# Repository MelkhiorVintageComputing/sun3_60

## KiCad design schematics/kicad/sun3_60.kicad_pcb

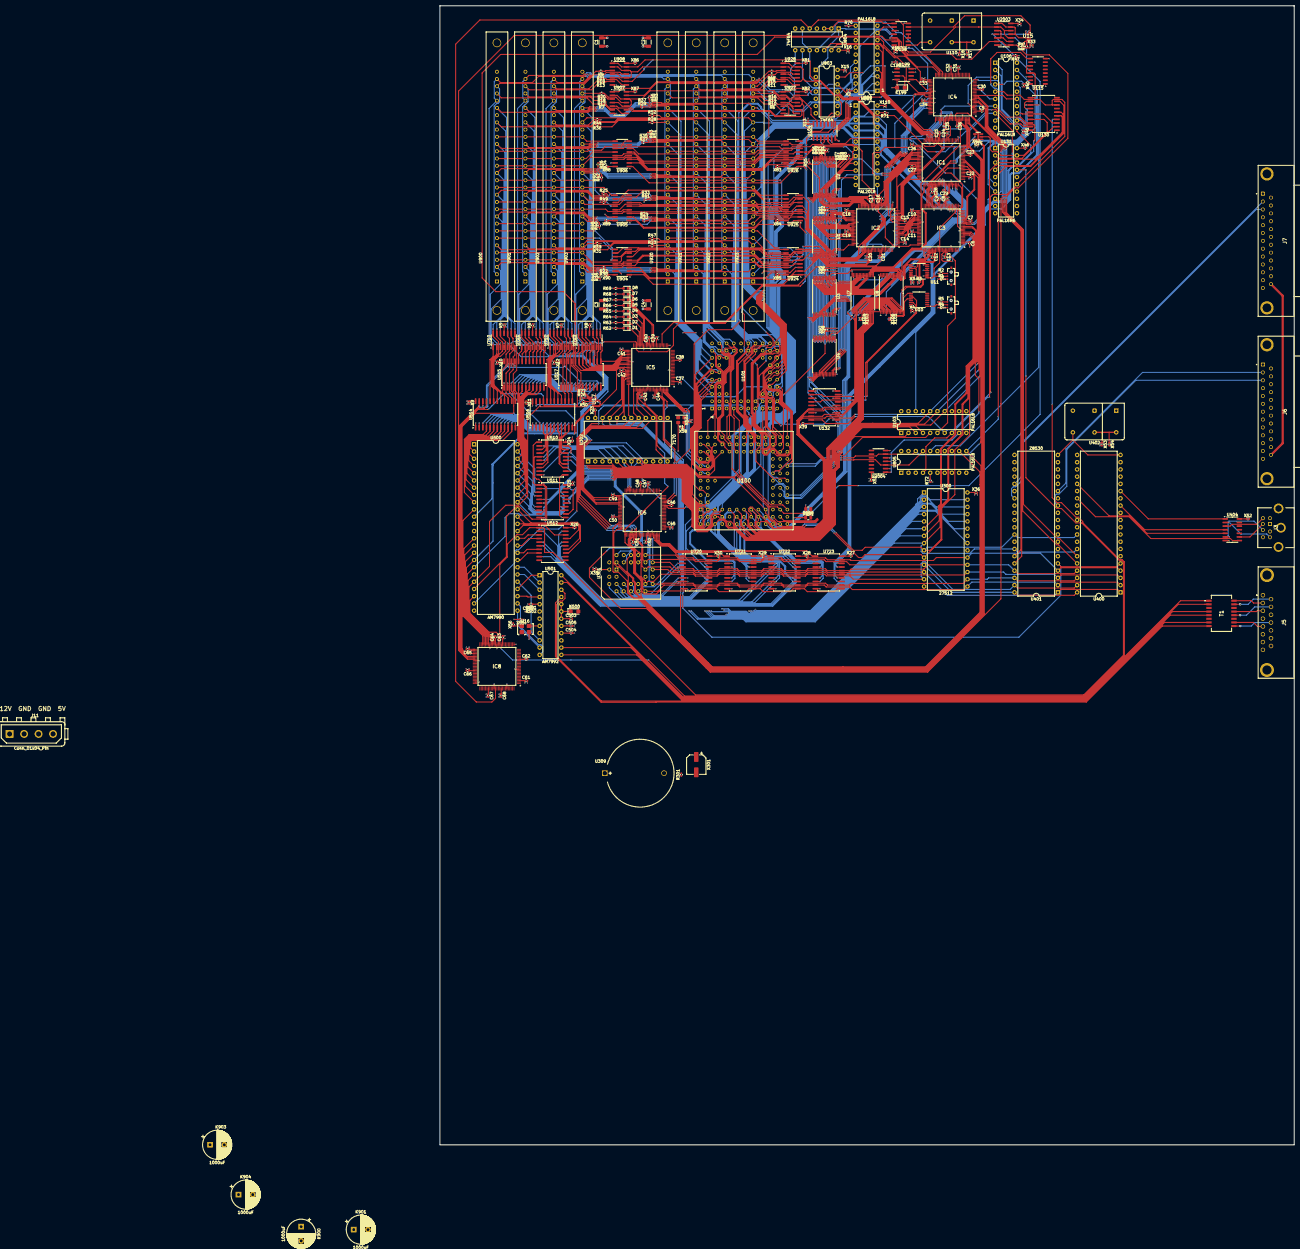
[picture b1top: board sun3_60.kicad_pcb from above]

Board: 4 copper layers, 300.0 x 400.0 mm, 317 parts (0 on the bottom side), 431 nets.

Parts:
C1, C2, C3, C4: 10uF 1206; C_1206_3216Metric
C5, C6, C7, C8, C9, C10, C11, C12, C13, C14, C15, C16, C17, C18, C19, C20, C21, C22, C23, C24, C25, C26, C27, C28, C29, C30, C31, C32, C33, C34, C35, C36, C37, C38, C39, C40, C41, C42, C43, C44, C45, C46, C47, C48, C49, C50, C51, C52, C61, C62, C63, C64, C65, C66, C67, C68, C199, C503, C504: 100nF 0402; C_0402_1005Metric
C502: 680 pF; C_0402_1005Metric
C505: 0.0056uF; C_0402_1005Metric
D1, D2, D3, D4, D5, D6, D7, D8: LED; LED_0603_1608Metric
IC1, IC2, IC3, IC4, IC5, IC6, IC8: ATF1504AS-10AU100; QFP50P1600X1600X120-100N
J3: Mini-DIN-8; 57492681
J5: 5747845-4; 57478454
J6, J7: DB25_Socket; D25S33E4PA00LF
J11: Conn_01x04_Pin; TE_MATE-N-LOK_350211-1_1x04_P5.08mm_Vertical
K199, K500: 10uF tantalum; CP_EIA-3216-18_Kemet-A
K900, K901, K903, K904: 1000uF; CP_Radial_D10.0mm_P5.00mm
R1, R2, R3, R4, R5: 10k; R_0402_1005Metric
R6, R7, R8, R9, R10, R11, R12, R13, R14, R15, R16, R17, R18, R19, R20, R21: 22; R_0402_1005Metric
R22, R23, R24, R25, R26, R27, R28, R29, R30, R31, R32, R33, R34, R35, R36, R37, R38, R39, R40, R41, R42, R43, R44, R45, R46, R47, R48, R49, R50, R51, R52, R53, R55, R56, R57, R58, R59, R60, R61, R70, R71, R72, R75, R76, R77, R78: 4.7k; R_0402_1005Metric
R62, R63, R64, R65, R66, R67, R68, R69: 510; R_0402_1005Metric
R100: 150 ohm 0805; R_0805_2012Metric
R101: 100 ohm 0805; R_0805_2012Metric
R301: 470-OHM; C_0402_1005Metric
R501: 510 Ohm; R_0402_1005Metric
R502: 3K Ohm; R_0402_1005Metric
S1, S2: SSAJ110100; SW_SSAJ110100
T1: TG01-0506NRLTR; TG010506NRLTR
U1, U2, U3, U4, U7, U8: IS61C5128AS-25HLI; TSOP-I-32_11.8x8mm_P0.5mm
U10: CBT3257APW; TSSOP-16_4.4x5mm_P0.65mm
U11: 74CBT3257APW; TSSOP-16_4.4x5mm_P0.65mm
U14: 74LVC1G04; SOT-23-5
U15, U17: 74LVC1G74; 74AVC9112GTX
U16: 20 MHz; Oscillator_SMD_SeikoEpson_SG8002LB-4Pin_5.0x3.2mm
U100: 68020; MC68020RC25
U101: 68881; MC68882_PGA
U103, U106, U800, U805: PAL16L8; DIP-20_W7.62mm
U104: 74F04; SOIC-14_3.9x8.7mm_P1.27mm
U108: 74F00; SOIC-14_3.9x8.7mm_P1.27mm
U110: 40.000 Mhz; CXO_DIP8+14
U115: 74LS590; SO-16_3.9x9.9mm_P1.27mm
U130: 74F374; SOIC-20W_7.5x12.8mm_P1.27mm
U131: PAL16R6; DIP-20_W7.62mm
U132: ALS244; SOIC-20W_7.5x12.8mm_P1.27mm
U199: 7705; SOIC-8_3.9x4.9mm_P1.27mm
U300: 27512; DIP-28_W15.24mm
U301: AT28C64B_PLCC; PLCC-32_THT-Socket
U302: 7170; DIP-24_W15.24mm
U309: 3-VOLT; BatteryHolder_MYOUNG_BS-07-A1BJ001_CR2032
U400, U401: Z8530; DIP-40_W15.24mm
U402: 4.9152 Mhz; CXO_DIP8+14
U404: 74ALS04; SOIC-14_3.9x8.7mm_P1.27mm
U500: AM7990; DIP-48_W15.24mm
U501: AM7992; DIP-24_W7.62mm
U510, U511, U512: ALS373; SOIC-20W_7.5x12.8mm_P1.27mm
U514, U515, U516, U517: ALS652; SOIC-24W_7.5x15.4mm_P1.27mm
U710, U711, U712, U713: ACT11286; SOIC-14_3.9x8.7mm_P1.27mm
U720, U721, U722, U723: ALS374; SOIC-20W_7.5x12.8mm_P1.27mm
U802: PAL20L8; DIP-24_W7.62mm
U803, U804: 74F64; DIP-14_W7.62mm
U900, U901, U902, U903, U920, U921, U922, U923: SIMM
U904, U905, U906, U924, U925, U926: 74AS258; SOIC-16_3.9x9.9mm_P1.27mm
U907, U908, U927, U928: AS1032; SOIC-14_3.9x8.7mm_P1.27mm
U2003: 74AS04; SOIC-14_3.9x8.7mm_P1.27mm
U2004: 74LS125; SOIC-14_3.9x8.7mm_P1.27mm
X2, X3, X4, X5, X6, X7, X8, X9, X10, X11, X12, X13, X14, X15, X16, X17, X23, X24, X25, X26, X27, X28, X29, X30, X33, X34, X35, X36, X39, X40, X41, X42, X46, X47, X50, X51, X52, X53, X55, X57, X81, X82, X83, X84, X85, X86, X87, X88, X89, X90, X91, X93, X95, X97, X103, X105, X110: 100nF 0402; C_0402_1005Metric
X18, X54, X56, X58, X92, X94, X96, X98, X104, X106: 10nF 0402; C_0402_1005Metric
X301: 470UF; CP_Elec_6.3x7.7
Y1: SiT8008xx-2x-xxS; Crystal_SMD_3225-4Pin_3.2x2.5mm

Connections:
+12V: J5.13, J11.1
-5V: J6.25, J7.25
/AS: IC1.40 (I/O_22), IC4.61 (I/O_34), U14.4, U103.9 (I9), U803.12 (A3), U804.9 (D1), U2004.1, U2004.4
/AS-: U14.2, U100.L1 (AS-), U101.H1 (AS-), U130.17 (D3), U131.19 (Q0)
/BERR-: IC8.30 (I/O_15), U100.J2 (BERR-), U106.18 (IO2)
/BERR.T-: IC3.17 (I/O_8), IC4.6 (I/O_1), U106.3 (I3)
/C.S3: IC4.60 (I/O_33), U804.12 (A3)
/C.S3-: IC1.44 (I/O_23), IC4.79 (I/O_44), U803.13 (A4), U805.3 (I3), U904.1 (S), U905.1 (S), U906.1 (S), U924.1 (S), U925.1 (S), U926.1 (S)
/C.S5: IC4.48 (I/O_27), U108.13
/CAS-: IC6.20 (I/O_10), U104.13, U804.8 (Y), U805.2 (I2), U908.2, U908.4, U908.10, U908.12, U928.2, U928.4, U928.10, U928.12
/CLK: IC6.87 (INPUT/GCLK1), U108.12, U803.1 (A1), U804.1 (A1), U2003.6, U2003.8
/CLK-: IC4.90 (INPUT/GCLK2), IC8.87 (INPUT/GCLK1), U115.11 (CPC), U115.13 (CPR), U130.11 (CLK), U131.1 (CLK), U804.5 (C2), U2003.2, U2003.10, U2003.12
/CX0: IC3.76 (I/O_43), U7.20 (A0), U8.17 (A3), U723.13 (D4)
/CX1: IC3.79 (I/O_44), U7.19 (A1), U8.18 (A2), U723.14 (D5)
/CX2: IC3.80 (I/O_45), U7.18 (A2), U8.19 (A1), U723.17 (D6)
/D0: R22.2, U100.K13 (D00), U101.A3 (D00), U514.20 (B1), U710.1 (P2), U900.3 (D0), U920.3 (D0)
/D1: R23.2, U100.K12 (D01), U101.A4 (D01), U514.19 (B2), U710.2 (P1), U900.6 (D1), U920.6 (D1)
/D2: R24.2, U100.L13 (D02), U101.B5 (D02), U514.18 (B3), U710.14 (P3), U900.10 (D2), U920.10 (D2)
/D3: R25.2, U100.L12 (D03), U101.A5 (D03), U514.17 (B4), U710.13 (P4), U900.13 (D3), U920.13 (D3)
/D4: R26.2, U100.M13 (D04), U101.A6 (D04), U514.16 (B5), U710.12 (P5), U900.16 (D4), U920.16 (D4)
/D5: R27.2, U100.M12 (D05), U101.B6 (D05), U514.15 (B6), U710.10 (P6), U900.20 (D5), U920.20 (D5)
/D6: R28.2, U100.M11 (D06), U101.A7 (D06), U514.14 (B7), U710.9 (P7), U900.23 (D6), U920.23 (D6)
/D7: R29.2, U100.L10 (D07), U101.A8 (D07), U514.13 (B8), U710.8, U900.25 (D7), U920.25 (D7)
/D8: R30.2, U100.N12 (D08), U101.A9 (D08), U515.20 (B1), U711.1 (P2), U901.3 (D0), U921.3 (D0)
/D9: R31.2, U100.N11 (D09), U101.C8 (D09), U515.19 (B2), U711.2 (P1), U901.6 (D1), U921.6 (D1)
/D10: R32.2, U100.M10 (D10), U101.B9 (D10), U515.18 (B3), U711.14 (P3), U901.10 (D2), U921.10 (D2)
/D11: R33.2, U100.L9 (D11), U101.B10 (D11), U515.17 (B4), U711.13 (P4), U901.13 (D3), U921.13 (D3)
/D12: R34.2, U100.N10 (D12), U101.D9 (D12), U515.16 (B5), U711.12 (P5), U901.16 (D4), U921.16 (D4)
/D13: R35.2, U100.M9 (D13), U101.C9 (D13), U515.15 (B6), U711.10 (P6), U901.20 (D5), U921.20 (D5)
/D14: R36.2, U100.N9 (D14), U101.C10 (D14), U515.14 (B7), U711.9 (P7), U901.23 (D6), U921.23 (D6)
/D15: R37.2, U100.L8 (D15), U101.D10 (D15), U515.13 (B8), U711.8, U901.25 (D7), U921.25 (D7)
/D16: R38.2, U100.M7 (D16), U101.F10 (D16), U516.20 (B1), U712.1 (P2), U902.3 (D0), U922.3 (D0)
/D17: R39.2, U100.N6 (D17), U101.F9 (D17), U516.19 (B2), U712.2 (P1), U902.6 (D1), U922.6 (D1)
/D18: R40.2, U100.M6 (D18), U101.G10 (D18), U516.18 (B3), U712.14 (P3), U902.10 (D2), U922.10 (D2)
/D19: R41.2, U100.L6 (D19), U101.H10 (D19), U516.17 (B4), U712.13 (P4), U902.13 (D3), U922.13 (D3)
/D20: R42.2, U100.N5 (D20), U101.G9 (D20), U516.16 (B5), U712.12 (P5), U902.16 (D4), U922.16 (D4)
/D21: R43.2, U100.M5 (D21), U101.J10 (D21), U516.15 (B6), U712.10 (P6), U902.20 (D5), U922.20 (D5)
/D22: R44.2, U100.N4 (D22), U101.K10 (D22), U516.14 (B7), U712.9 (P7), U902.23 (D6), U922.23 (D6)
/D23: R45.2, U100.L5 (D23), U101.J9 (D23), U516.13 (B8), U712.8, U902.25 (D7), U922.25 (D7)
/D24: IC3.33 (I/O_18), IC5.63 (I/O_35), R46.2, U100.M4 (D24), U101.K9 (D24), U517.20 (B1), U713.1 (P2), U903.3 (D0), U923.3 (D0)
/D25: IC3.32 (I/O_17), IC5.61 (I/O_34), R47.2, U100.N3 (D25), U101.J7 (D25), U517.19 (B2), U713.2 (P1), U903.6 (D1), U923.6 (D1)
/D26: IC3.31 (I/O_16), IC5.60 (I/O_33), R48.2, U100.M3 (D26), U101.K8 (D26), U517.18 (B3), U713.14 (P3), U903.10 (D2), U923.10 (D2)
/D27: IC3.30 (I/O_15), IC5.58 (I/O_32), R49.2, U100.L4 (D27), U101.K7 (D27), U517.17 (B4), U713.13 (P4), U903.13 (D3), U923.13 (D3)
/D28: IC3.29 (I/O_14), IC5.57 (I/O_31), R50.2, U100.N2 (D28), U101.J6 (D28), U517.16 (B5), U713.12 (P5), U903.16 (D4), U923.16 (D4)
/D29: IC3.21 (I/O_11), IC5.56 (I/O_30), R51.2, U100.M2 (D29), U101.K6 (D29), U517.15 (B6), U713.10 (P6), U903.20 (D5), U923.20 (D5)
/D30: IC3.23 (I/O_12), IC5.54 (I/O_29), R52.2, U100.L3 (D30), U101.K5 (D30), U517.14 (B7), U713.9 (P7), U903.23 (D6), U923.23 (D6)
/D31: IC3.25 (I/O_13), IC5.52 (I/O_28), R53.2, U100.N1 (D31), U101.J5 (D31), U517.13 (B8), U713.8, U903.25 (D7), U923.25 (D7)
/DIS.RAS-: IC1.41 (I/0), U803.11 (A2)
/DISACC-: IC1.45 (I/O_24), IC4.87 (INPUT/GCLK1), U804.13 (A4)
/DMA: U106.12 (IO8), U723.18 (D7)
/DS-: IC4.63 (I/O_35), IC8.67 (I/O_38), U100.M1 (DS-), U101.G1 (DS-)
/DSACK0-: IC1.21 (I/O_11), IC4.94 (I/O_51), IC5.6 (I/O_1), U100.H3 (DSACK0-), U101.J4 (DSACK0-), U106.17 (I03), U805.18 (IO2), U2004.6
/DSACK1-: IC8.16 (I/O_7), U100.J1 (DSACK1-), U101.K4 (DSACK1-), U805.17 (I03), U2004.3
/DXACK-: U130.13 (D7), U805.16 (IO4)
/E.ACK-: IC8.36 (I/O_20), U131.17 (Q2), U510.1 (OE-), U511.1 (OE-), U512.1 (OE-)
/E.CS-: IC8.40 (I/O_22), U17.1 (C), U100.G1 (ECS-), U500.20 (CS-), U516.22 (SBA), U517.22 (SBA)
/E.HOLD-: IC8.44 (I/O_23), U17.2 (D), U500.17 (HOLD-)
/E.IRQ-: IC5.65 (I/O_37), U500.11 (INT-)
/E.REQ-: IC8.35 (I/O_19), U130.4 (D2)
/EN.CAS: IC4.47 (I/O_26), U804.11 (A2)
/EN.DEV-: IC1.23 (I/O_12), IC1.25 (I/O_13), IC4.93 (I/O_50), IC6.30 (I/O_15)
/EN.E-: IC4.45 (I/O_24), IC8.58 (I/O_32)
/EN.UART-: IC1.20 (I/O_10), IC4.8 (I/O_2)
/Ethernet/A0: IC1.48 (I/O_27), IC3.14 (I/O_6), IC6.46 (I/O_25), U100.C4 (A00), U300.10 (A0), U301.11 (A0), U302.8 (A0), U510.2 (Q0), U720.3 (D0), U800.3 (I3)
/Ethernet/A1: IC1.47 (I/O_26), IC3.13 (I/O_5), IC6.47 (I/O_26), U100.A2 (A01), U101.K1 (A01), U300.9 (A1), U301.10 (A1), U302.7 (A1), U400.32 (D/~C), U401.32 (D/~C), U500.21 (ADR), U510.5 (Q1), U720.4 (D1), U800.4 (I4)
/Ethernet/A2: IC3.10 (I/O_4), IC6.48 (I/O_27), U100.E12 (A02), U101.H2 (A02), U300.8 (A2), U301.9 (A2), U302.6 (A2), U400.34 (A/~B), U401.34 (A/~B), U510.6 (Q2), U720.7 (D2), U906.13 (4B), U926.13 (4B)
/Ethernet/A3: IC3.9 (I/O_3), U100.D13 (A03), U101.J1 (A03), U300.7 (A3), U301.8 (A3), U302.5 (A3), U510.9 (Q3), U720.8 (D3), U906.6 (2B), U926.6 (2B)
/Ethernet/A4: IC3.8 (I/O_2), U100.D12 (A04), U101.G2 (A04), U300.6 (A4), U301.7 (A4), U302.4 (A4), U510.12 (Q4), U720.13 (D4), U904.3 (1B), U924.3 (1B)
/Ethernet/A5: U100.C13 (A05), U300.5 (A5), U301.6 (A5), U510.15 (Q5), U720.14 (D5), U904.6 (2B), U924.6 (2B)
/Ethernet/A6: U100.B13 (A06), U300.4 (A6), U301.5 (A6), U510.16 (Q6), U720.17 (D6), U904.10 (3B), U924.10 (3B)
/Ethernet/A7: U100.C12 (A07), U300.3 (A7), U301.4 (A7), U510.19 (Q7), U720.18 (D7), U904.13 (4B), U924.13 (4B)
/Ethernet/A8: U100.A13 (A08), U300.25 (A8), U301.24 (A10), U511.2 (Q0), U721.3 (D0), U905.3 (1B), U925.3 (1B)
/Ethernet/A9: U100.C11 (A09), U300.24 (A9), U301.28 (A9), U511.5 (Q1), U721.4 (D1), U905.6 (2B), U925.6 (2B)
/Ethernet/A10: U100.B12 (A10), U300.21 (A10), U301.29 (A8), U511.6 (Q2), U721.7 (D2), U905.10 (3B), U925.10 (3B)
/Ethernet/A11: U100.A12 (A11), U300.23 (A11), U511.9 (Q3), U721.8 (D3), U905.13 (4B), U925.13 (4B)
/Ethernet/A12: U100.C10 (A12), U300.2 (A12), U511.12 (Q4), U721.13 (D4), U906.3 (1B), U926.3 (1B)
/Ethernet/A13: U1.19 (A1), U2.19 (A1), U3.19 (A1), U4.19 (A1), U100.B11 (A13), U103.1 (I1), U300.26 (A13), U511.15 (Q5), U721.14 (D5)
/Ethernet/A14: U1.20 (A0), U2.20 (A0), U3.20 (A0), U4.20 (A0), U100.A11 (A14), U103.2 (I2), U300.27 (A14), U511.16 (Q6), U721.17 (D6)
/Ethernet/A15: U1.18 (A2), U2.18 (A2), U3.18 (A2), U4.18 (A2), U100.B10 (A15), U103.3 (I3), U300.1 (A15), U511.19 (Q7), U721.18 (D7)
/Ethernet/A16: U1.17 (A3), U2.17 (A3), U3.17 (A3), U4.17 (A3), U100.C9 (A16), U103.4 (I4), U512.12 (Q4), U722.3 (D0)
/Ethernet/A17: U7.14 (A6), U8.3 (A8), U100.C8 (A17), U103.5 (I5), U512.15 (Q5), U722.4 (D1)
/Ethernet/A18: U7.15 (A5), U8.2 (A9), U100.B8 (A18), U512.16 (Q6), U722.7 (D2)
/Ethernet/A19: U7.16 (A4), U8.1 (A11), U100.A8 (A19), U512.19 (Q7), U722.8 (D3)
/Ethernet/A20: U7.12 (A12), U8.6 (A18), U100.B7 (A20), U512.2 (Q0), U722.13 (D4)
/Ethernet/A21: U7.11 (A14), U8.7 (A15), U100.C7 (A21), U512.5 (Q1), U722.14 (D5)
/Ethernet/A22: U7.13 (A7), U8.4 (A13), U100.A7 (A22), U512.6 (Q2), U722.17 (D6)
/Ethernet/A23: U7.10 (A16), U8.9 (A17), U100.A6 (A23), U512.9 (Q3), U722.18 (D7)
/Ethernet/A24: U7.31 (A10), U8.31 (A10), U100.B6 (A24), U132.16 (1Y2), U723.3 (D0)
/Ethernet/A25: U7.9 (A17), U8.10 (A16), U100.C6 (A25), U132.3 (2Y4), U723.4 (D1)
/Ethernet/A26: U7.3 (A8), U8.14 (A6), U100.A5 (A26), U132.5 (2Y3), U723.7 (D2)
/Ethernet/A27: U7.4 (A13), U8.13 (A7), U100.B5 (A27), U132.18 (1Y1), U723.8 (D3)
/Ethernet/A28: IC1.90 (INPUT/GCLK2), U10.14, U100.A4 (A28), U132.14 (1Y3)
/Ethernet/A29: IC1.89 (INPUT/GCLR), U100.C5 (A29), U132.7 (2Y2)
/Ethernet/A30: IC1.88 (INPUT/OE1), U10.11, U100.B4 (A30), U132.12 (1Y4)
/Ethernet/A31: IC1.87 (INPUT/GCLK1), U100.A3 (A31), U132.9 (2Y1)
/Ethernet/CLK_20MHZ_ETH: U16.3 (OUT), U501.8 (X1)
/Ethernet/E.A16: U500.39 (A16), U512.13 (D4)
/Ethernet/E.A17: U500.38 (A17), U512.14 (D5)
/Ethernet/E.A18: U500.37 (A18), U512.17 (D6)
/Ethernet/E.A19: U500.36 (A19), U512.18 (D7)
/Ethernet/E.A20: U500.35 (A20), U512.3 (D0)
/Ethernet/E.A21: U500.34 (A21), U512.4 (D1)
/Ethernet/E.A22: U500.33 (A22), U512.7 (D2)
/Ethernet/E.A23: U500.32 (A23), U512.8 (D3)
/Ethernet/E.ALE: IC8.42 (I/O/PD2), U500.18 (ALE), U510.11 (LE), U511.11 (LE), U512.11 (LE)
/Ethernet/E.BM0-: IC8.46 (I/O_25), U500.15 (LDB-)
/Ethernet/E.BM1-: IC8.45 (I/O_24), U500.16 (VDB-)
/Ethernet/E.CBA: IC8.57 (I/O_31), U514.23 (CBA), U515.23 (CBA), U516.23 (CBA), U517.23 (CBA)
/Ethernet/E.CLSW: U500.28 (COLL), U501.1 (COLL)
/Ethernet/E.CO+: T1.1 (PRI_1), U501.24 (COL+)
/Ethernet/E.CO+<>: J5.2, T1.16 (SEC_6)
/Ethernet/E.CO-: T1.2 (PRI_2), U501.23 (COL-)
/Ethernet/E.CO-<>: J5.9, T1.15 (SEC_5)
/Ethernet/E.D0: U500.9 (DA00), U510.3 (D0), U514.4 (A1), U516.4 (A1)
/Ethernet/E.D1: U500.8 (DA01), U510.4 (D1), U514.5 (A2), U516.5 (A2)
/Ethernet/E.D2: U500.7 (DA02), U510.7 (D2), U514.6 (A3), U516.6 (A3)
/Ethernet/E.D3: U500.6 (DA03), U510.8 (D3), U514.7 (A4), U516.7 (A4)
/Ethernet/E.D4: U500.5 (DA04), U510.13 (D4), U514.8 (A5), U516.8 (A5)
/Ethernet/E.D5: U500.4 (DA05), U510.14 (D5), U514.9 (A6), U516.9 (A6)
/Ethernet/E.D6: U500.3 (DA06), U510.17 (D6), U514.10 (A7), U516.10 (A7)
/Ethernet/E.D7: U500.2 (DA07), U510.18 (D7), U514.11 (A8), U516.11 (A8)
/Ethernet/E.D8: U500.47 (DA08), U511.3 (D0), U515.4 (A1), U517.4 (A1)
/Ethernet/E.D9: U500.46 (DA09), U511.4 (D1), U515.5 (A2), U517.5 (A2)
/Ethernet/E.D10: U500.45 (DA10), U511.7 (D2), U515.6 (A3), U517.6 (A3)
/Ethernet/E.D11: U500.44 (DA11), U511.8 (D3), U515.7 (A4), U517.7 (A4)
/Ethernet/E.D12: U500.43 (DA12), U511.13 (D4), U515.8 (A5), U517.8 (A5)
/Ethernet/E.D13: U500.42 (DA13), U511.14 (D5), U515.9 (A6), U517.9 (A6)
/Ethernet/E.D14: U500.41 (DA14), U511.17 (D6), U515.10 (A7), U517.10 (A7)
/Ethernet/E.D15: U500.40 (DA15), U511.18 (D7), U515.11 (A8), U517.11 (A8)
/Ethernet/E.DAS-: IC8.47 (I/O_26), U500.14 (DAS-)
/Ethernet/E.GAB: IC8.52 (I/O_28), U514.3 (GAB), U515.3 (GAB), U516.3 (GAB), U517.3 (GAB)
/Ethernet/E.GBA0-: IC8.54 (I/O_29), U516.21 (G-BA), U517.21 (G-BA)
/Ethernet/E.GBA1-: IC8.56 (I/O_30), U514.21 (G-BA), U515.21 (G-BA)
/Ethernet/E.HLDA-: IC8.41 (I/0), U500.19 (HLDA-)
/Ethernet/E.RCLK: U500.27 (RCLK), U501.4 (RCLK)
/Ethernet/E.RDY-: IC8.37 (I/O_21), U500.22 (RDY-)
/Ethernet/E.RENA: U500.30 (RXE), U501.3 (RXE)
/Ethernet/E.RX: U500.31 (RX), U501.2 (RX)
/Ethernet/E.RX+: T1.7 (PRI_5), U501.22 (RXD+)
/Ethernet/E.RX+<>: J5.5, T1.10 (SEC_2)
/Ethernet/E.RX-: T1.8 (PRI_6), U501.21 (RXD-)
/Ethernet/E.RX-<>: J5.12, T1.9 (SEC_1)
/Ethernet/E.TCLK: U500.25 (TCLK), U501.11 (TCLK)
/Ethernet/E.TENA: U500.26 (TXE), U501.12 (TXE)
/Ethernet/E.TX: U500.29 (TX), U501.10 (TX)
/Ethernet/E.TX+: T1.4 (PRI_3), U501.14 (TXD+)
/Ethernet/E.TX+<>: J5.3, T1.13 (SEC_4)
/Ethernet/E.TX-: T1.5 (PRI_4), U501.13 (TXD-)
/Ethernet/E.TX-<>: J5.10, T1.12 (SEC_3)
/Ethernet/E.WE-: IC8.48 (I/O_27), U500.10 (R/W-)
/FC0: IC1.10 (I/O_4), U100.E1 (FC0), U103.16 (IO4)
/FC1: IC1.13 (I/O_5), U100.F3 (FC1), U103.15 (IO5)
/FC2: IC1.14 (I/O_6), U100.F2 (FC2), U103.14 (IO6)
/HALT-: IC4.14 (I/O_6), U100.K2 (HALT-), U106.15 (IO5)
/INIT-: IC3.16 (I/O_7), IC4.25 (I/O_13), IC5.84 (I/O_48), IC6.76 (I/O_43), U106.11 (I10), U131.8 (I6), U805.11 (I10)
/IO2CPU-: IC4.92 (I/O_49), IC5.30 (I/O_15)
/IOLOCK-: IC4.52 (I/O_28), U17.5 (Q)
/IPL0-: IC5.100 (I/O_56), U100.J12 (IPL0-)
/IPL1-: IC5.99 (I/O_55), U100.J13 (IPL1-)
/IPL2-: IC5.98 (I/O_54), U100.H12 (IPL2-)
/OE.BOOT-: IC1.33 (I/O_18), IC4.83 (I/O_47)
/P0: U713.3 (P_I/O), U903.26 (O8), U903.29 (I8), U923.26 (O8), U923.29 (I8)
/P1: U712.3 (P_I/O), U902.26 (O8), U902.29 (I8), U922.26 (O8), U922.29 (I8)
/P2: U711.3 (P_I/O), U901.26 (O8), U901.29 (I8), U921.26 (O8), U921.29 (I8)
/P3: U710.3 (P_I/O), U900.26 (O8), U900.29 (I8), U920.26 (O8), U920.29 (I8)
/PD0-: U7.30 (~CE), U8.30 (~CE)
/PD1-: U1.30 (~CE), U2.30 (~CE), U3.30 (~CE), U4.30 (~CE)
/POR-: IC4.58 (I/O_32), U199.5 (RES-)
/R.ACK-: IC1.52 (I/O_28), U103.8 (I8), U106.8 (I8), U108.9, U131.18 (Q1), U800.9 (I9), U802.14 (I14), U805.4 (I4)
/READ-: IC2.36 (I/O_20), IC3.75 (I/O_42), U104.4, U104.5, U906.11 (3A), U926.11 (3A)
/RERUN-: IC4.21 (I/O_11), IC8.93 (I/O_50), U106.6 (I6)
/RESET-: IC5.97 (I/O_53), U100.C1 (RESET-), U101.D1 (RESET-), U106.14 (IO6), U500.23 (RESET-)
/RTC-: IC5.81 (I/O_46), U302.12 (INT-)
/R/W-: IC6.17 (I/O_8), IC8.17 (I/O_8), U100.L2 (R/W-), U101.K2 (R/W-), U104.3
/S8A Memory/CAS: U104.12, U804.6 (C3), U804.10 (D2)
/S8A Memory/CAS0-: U802.22 (IO22), U908.1, U908.5, U908.9, U908.13
/S8A Memory/CAS1-: U802.21 (IO21), U928.1, U928.5, U928.9, U928.13
/S8A Memory/CE-: U802.15 (IO15), U805.1 (I1)
/S8A Memory/M.PDa-: R70.2, U800.11 (I10)
/S8A Memory/M.PDb-: R71.2, U802.23 (I23)
/S8A Memory/M.PDc-: R72.2, U805.5 (I5)
/S8A Memory/PA13: IC2.92 (I/O_49), U1.21 (I/O0), U904.2 (1A), U924.2 (1A)
/S8A Memory/PA14: IC2.85 (I/O/GCLK3), U1.22 (I/O1), U904.5 (2A), U924.5 (2A)
/S8A Memory/PA15: IC2.84 (I/O_48), U1.23 (I/O2), U904.11 (3A), U924.11 (3A)
/S8A Memory/PA16: IC2.83 (I/O_47), U1.25 (I/O3), U904.14 (4A), U924.14 (4A)
/S8A Memory/PA17: IC2.81 (I/O_46), IC4.67 (I/O_38), U1.26 (I/O4), U905.2 (1A), U925.2 (1A)
/S8A Memory/PA18: IC2.80 (I/O_45), IC4.68 (I/O_39), U1.27 (I/O5), U905.14 (4A), U925.14 (4A)
/S8A Memory/PA19: IC2.79 (I/O_44), IC4.69 (I/O_40), U1.28 (I/O6), U905.5 (2A), U925.5 (2A)
/S8A Memory/PA20: IC2.76 (I/O_43), IC4.71 (I/O_41), U1.29 (I/O7), U905.11 (3A), U925.11 (3A)
/S8A Memory/PA21: IC2.48 (I/O_27), U2.21 (I/O0), U906.2 (1A), U926.2 (1A)
/S8A Memory/PA22: IC2.47 (I/O_26), U2.22 (I/O1), U802.7 (I7), U906.5 (2A), U926.5 (2A)
/S8A Memory/PA23: IC2.46 (I/O_25), U2.23 (I/O2), U802.8 (I8), U906.14 (4A), U926.14 (4A)
/S8A Memory/PA24: IC2.45 (I/O_24), U2.25 (I/O3), U802.9 (I9)
/S8A Memory/PA25: IC2.44 (I/O_23), U2.26 (I/O4), U802.10 (I10)
/S8A Memory/PA26: IC2.41 (I/0), U2.27 (I/O5), U802.11 (I11)
/S8A Memory/PA27: IC2.40 (I/O_22), U2.28 (I/O6), U802.13 (I13)
/S8A Memory/PA28: IC2.37 (I/O_21), IC4.64 (I/O_36), U2.29 (I/O7)
/S8A Memory/R.ACK: U108.8, U804.2 (B1), U804.3 (B2)
/S8A Memory/RAS: U104.10, U803.10 (D2)
/S8A Memory/RAS-: U104.11, U803.8 (Y), U907.2, U907.4, U907.10, U907.12, U927.2, U927.4, U927.10, U927.12
/S8A Memory/RE00-: U800.19 (IO1), U907.5, U927.5
/S8A Memory/RE01-: U800.18 (IO2), U907.9, U927.9
/S8A Memory/RE02-: U800.17 (I03), U907.1, U927.1
/S8A Memory/RE03-: U800.16 (IO4), U907.13, U927.13
/SCC.IRQ-: IC5.92 (I/O_49), U400.5 (~INT), U401.5 (~INT)
/SCSI 2, Parity/IO.D0: IC5.80 (I/O_45), IC6.84 (I/O_48), U300.11 (D0), U301.22 (D7), U302.15 (D0), U400.40 (D0), U401.40 (D0), U720.2 (Q0), U721.2 (Q0), U722.2 (Q0), U723.2 (Q0)
/SCSI 2, Parity/IO.D1: IC5.79 (I/O_44), IC6.83 (I/O_47), U300.12 (D1), U301.19 (D4), U302.16 (D1), U400.1 (D1), U401.1 (D1), U720.5 (Q1), U721.5 (Q1), U722.5 (Q1), U723.5 (Q1)
/SCSI 2, Parity/IO.D2: IC5.76 (I/O_43), IC6.81 (I/O_46), U300.13 (D2), U301.15 (D2), U302.17 (D2), U400.39 (D2), U401.39 (D2), U720.6 (Q2), U721.6 (Q2), U722.6 (Q2), U723.6 (Q2)
/SCSI 2, Parity/IO.D3: IC5.75 (I/O_42), IC6.80 (I/O_45), U300.15 (D3), U301.13 (D0), U302.18 (D3), U400.2 (D3), U401.2 (D3), U720.9 (Q3), U721.9 (Q3), U722.9 (Q3), U723.9 (Q3)
/SCSI 2, Parity/IO.D4: IC5.71 (I/O_41), IC6.93 (I/O_50), U300.16 (D4), U301.14 (D1), U302.19 (D4), U400.38 (D4), U401.38 (D4), U720.12 (Q4), U721.12 (Q4), U722.12 (Q4), U723.12 (Q4)
/SCSI 2, Parity/IO.D5: IC5.69 (I/O_40), IC6.94 (I/O_51), U300.17 (D5), U301.18 (D3), U302.20 (D5), U400.3 (D5), U401.3 (D5), U720.15 (Q5), U721.15 (Q5), U722.15 (Q5), U723.15 (Q5)
/SCSI 2, Parity/IO.D6: IC5.68 (I/O_39), IC6.96 (I/O_52), U300.18 (D6), U301.20 (D5), U302.21 (D6), U400.37 (D6), U401.37 (D6), U720.16 (Q6), U721.16 (Q6), U722.16 (Q6), U723.16 (Q6)
/SCSI 2, Parity/IO.D7: IC5.67 (I/O_38), IC6.92 (I/O_49), U300.19 (D7), U301.21 (D6), U302.22 (D7), U400.4 (D7), U401.4 (D7), U720.19 (Q7), U721.19 (Q7), U722.19 (Q7), U723.19 (Q7)
/SCSI 2, Parity/PAR0-: IC6.52 (I/O_28), U713.5 (P_ERR)
/SCSI 2, Parity/PAR1-: IC6.54 (I/O_29), U712.5 (P_ERR)
/SCSI 2, Parity/PAR2-: IC6.56 (I/O_30), U711.5 (P_ERR)
/SCSI 2, Parity/PAR3-: IC6.57 (I/O_31), U710.5 (P_ERR)
/SCSI 2, Parity/PAR.IRQ-: IC5.93 (I/O_50), IC6.21 (I/O_11)
/SCSI 2, Parity/PAR.SAMPLE: IC6.79 (I/O_44), U720.11 (CLK), U721.11 (CLK), U722.11 (CLK), U723.11 (CLK)
/SCSI 2, Parity/PAR.TEST-: IC6.23 (I/O_12), U710.7 (P9)
/SCSI 2, Parity/RD.PAR4-: IC6.100 (I/O_56), U723.1 (OE-)
/SCSI 2, Parity/RD.PAR5-: IC6.99 (I/O_55), U722.1 (OE-)
/SCSI 2, Parity/RD.PAR6-: IC6.98 (I/O_54), U721.1 (OE-)
/SCSI 2, Parity/RD.PAR7-: IC6.97 (I/O_53), U720.1 (OE-)
/SCSI 2, Parity/RD_PARX-: IC4.99 (I/O_55), IC6.75 (I/O_42)
/SCSI 2, Parity/WR_PARX-: IC4.100 (I/O_56), IC6.71 (I/O_41)
/SIMMs 1/CE00-: R9.1, U908.3
/SIMMs 1/CE01-: R13.1, U908.6
/SIMMs 1/CE02-: R19.1, U908.8
/SIMMs 1/CE03-: R21.1, U908.11
/SIMMs 1/M.A0.0: U900.4 (A0), U901.4 (A0), U902.4 (A0), U903.4 (A0), U904.4 (1Y)
/SIMMs 1/M.A1.0: U900.5 (A1), U901.5 (A1), U902.5 (A1), U903.5 (A1), U904.7 (2Y)
/SIMMs 1/M.A2.0: U900.7 (A2), U901.7 (A2), U902.7 (A2), U903.7 (A2), U904.9 (3Y)
/SIMMs 1/M.A3.0: U900.8 (A3), U901.8 (A3), U902.8 (A3), U903.8 (A3), U904.12 (4Y)
/SIMMs 1/M.A4.0: U900.11 (A4), U901.11 (A4), U902.11 (A4), U903.11 (A4), U905.4 (1Y)
/SIMMs 1/M.A5.0: U900.12 (A5), U901.12 (A5), U902.12 (A5), U903.12 (A5), U905.7 (2Y)
/SIMMs 1/M.A6.0: U900.14 (A6), U901.14 (A6), U902.14 (A6), U903.14 (A6), U905.9 (3Y)
/SIMMs 1/M.A7.0: U900.15 (A7), U901.15 (A7), U902.15 (A7), U903.15 (A7), U905.12 (4Y)
/SIMMs 1/M.A8.0: U900.17 (A8), U901.17 (A8), U902.17 (A8), U903.17 (A8), U906.4 (1Y)
/SIMMs 1/M.A9.0: U900.18 (A9), U901.18 (A9), U902.18 (A9), U903.18 (A9), U906.12 (4Y)
/SIMMs 1/M.A10.0: U900.19 (A10), U901.19 (A10), U902.19 (A10), U903.19 (A10), U906.7 (2Y)
/SIMMs 1/M.CE00-: R9.2, U900.2 (CS-), U900.28 (CS8-)
/SIMMs 1/M.CE01-: R13.2, U901.2 (CS-), U901.28 (CS8-)
/SIMMs 1/M.CE02-: R19.2, U902.2 (CS-), U902.28 (CS8-)
/SIMMs 1/M.CE03-: R21.2, U903.2 (CS-), U903.28 (CS8-)
/SIMMs 1/M.RE00-: R7.2, U900.27 (RAS-)
/SIMMs 1/M.RE01-: R12.2, U901.27 (RAS-)
/SIMMs 1/M.RE02-: R18.2, U902.27 (RAS-)
/SIMMs 1/M.RE03-: R20.2, U903.27 (RAS-)
/SIMMs 1/M.WE.0-: U900.21 (WE-), U901.21 (WE-), U902.21 (WE-), U903.21 (WE-), U906.9 (3Y)
/SIMMs 1/XE00-: R7.1, U907.6
/SIMMs 1/XE01-: R12.1, U907.8
/SIMMs 1/XE02-: R18.1, U907.3
/SIMMs 1/XE03-: R20.1, U907.11
/SIMMs 2/CE00-: R8.1, U928.3
/SIMMs 2/CE01-: R11.1, U928.6
/SIMMs 2/CE02-: R15.1, U928.8
/SIMMs 2/CE03-: R17.1, U928.11
/SIMMs 2/M.A0.0: U920.4 (A0), U921.4 (A0), U922.4 (A0), U923.4 (A0), U924.4 (1Y)
/SIMMs 2/M.A1.0: U920.5 (A1), U921.5 (A1), U922.5 (A1), U923.5 (A1), U924.7 (2Y)
/SIMMs 2/M.A2.0: U920.7 (A2), U921.7 (A2), U922.7 (A2), U923.7 (A2), U924.9 (3Y)
/SIMMs 2/M.A3.0: U920.8 (A3), U921.8 (A3), U922.8 (A3), U923.8 (A3), U924.12 (4Y)
/SIMMs 2/M.A4.0: U920.11 (A4), U921.11 (A4), U922.11 (A4), U923.11 (A4), U925.4 (1Y)
/SIMMs 2/M.A5.0: U920.12 (A5), U921.12 (A5), U922.12 (A5), U923.12 (A5), U925.7 (2Y)
/SIMMs 2/M.A6.0: U920.14 (A6), U921.14 (A6), U922.14 (A6), U923.14 (A6), U925.9 (3Y)
/SIMMs 2/M.A7.0: U920.15 (A7), U921.15 (A7), U922.15 (A7), U923.15 (A7), U925.12 (4Y)
/SIMMs 2/M.A8.0: U920.17 (A8), U921.17 (A8), U922.17 (A8), U923.17 (A8), U926.4 (1Y)
/SIMMs 2/M.A9.0: U920.18 (A9), U921.18 (A9), U922.18 (A9), U923.18 (A9), U926.12 (4Y)
/SIMMs 2/M.A10.0: U920.19 (A10), U921.19 (A10), U922.19 (A10), U923.19 (A10), U926.7 (2Y)
/SIMMs 2/M.CE00-: R8.2, U920.2 (CS-), U920.28 (CS8-)
/SIMMs 2/M.CE01-: R11.2, U921.2 (CS-), U921.28 (CS8-)
/SIMMs 2/M.CE02-: R15.2, U922.2 (CS-), U922.28 (CS8-)
/SIMMs 2/M.CE03-: R17.2, U923.2 (CS-), U923.28 (CS8-)
/SIMMs 2/M.RE00-: R6.2, U920.27 (RAS-)
/SIMMs 2/M.RE01-: R10.2, U921.27 (RAS-)
/SIMMs 2/M.RE02-: R14.2, U922.27 (RAS-)
/SIMMs 2/M.RE03-: R16.2, U923.27 (RAS-)
/SIMMs 2/M.WE.0-: U920.21 (WE-), U921.21 (WE-), U922.21 (WE-), U923.21 (WE-), U926.9 (3Y)
/SIMMs 2/XE00-: R6.1, U927.6
/SIMMs 2/XE01-: R10.1, U927.8
/SIMMs 2/XE02-: R14.1, U927.3
/SIMMs 2/XE03-: R16.1, U927.11
/SIZ0: IC8.20 (I/O_10), U100.F1 (SIZ0), U800.1 (I1)
/SIZ1: IC8.19 (I/O_9), U100.G2 (SIZ1), U800.2 (I2)
/V.INT-: IC5.96 (I/O_52), U805.12 (IO8)
/WDOG-: IC3.12 (I/O/PD1), IC4.76 (I/O_43)
/WRITE-: IC1.46 (I/O_25), IC4.88 (INPUT/OE1), IC5.48 (I/O_27), U104.6, U710.6 (XMIT-), U711.6 (XMIT-), U711.7 (P9), U712.6 (XMIT-), U712.7 (P9), U713.6 (XMIT-), U713.7 (P9), U800.7 (I7)
/XACK-: IC6.33 (I/O_18), IC8.29 (I/O_14), U130.15 (Q5), U131.7 (I5)
/sun3_60_cpu/BACK-: U100.A1 (BGACK-), U131.13 (Q6)
/sun3_60_cpu/BERR.P-: IC1.80 (I/O_45), IC3.47 (I/O_26), U106.2 (I2)
/sun3_60_cpu/BERR.V-: IC1.81 (I/O_46), IC3.46 (I/O_25), U106.1 (I1)
/sun3_60_cpu/BERRCLK: IC3.90 (INPUT/GCLK2), U106.19 (IO1)
/sun3_60_cpu/BG-: U100.B2 (BG-), U131.9 (I7)
/sun3_60_cpu/BR-: U100.B3 (BR-), U131.14 (Q5)
/sun3_60_cpu/C.S5-: IC1.42 (I/O/PD2), IC4.80 (I/O_45), U106.7 (I7), U130.18 (D1)
/sun3_60_cpu/C.S7X-: IC1.36 (I/O_20), U130.19 (Q1)
/sun3_60_cpu/CLK1: R100.2, R101.1, U100.C2 (CLK), U101.C2 (CLK), U2003.4
/sun3_60_cpu/CLK2X: U15.1 (C), U108.6
/sun3_60_cpu/CLKA: U15.5 (Q), U2003.1, U2003.11, U2003.13
/sun3_60_cpu/CLKA-: U15.2 (D), U15.3 (~Q), U2003.3, U2003.5, U2003.9
/sun3_60_cpu/CS.FPP-: U101.J3 (CS-), U103.17 (I03)
/sun3_60_cpu/DMA-: U103.7 (I7), U106.5 (I5), U130.8 (D6), U131.15 (Q4), U132.1 (EN1-), U132.19 (EN2-)
/sun3_60_cpu/DMAX-: U130.9 (Q6), U131.5 (I3)
/sun3_60_cpu/E.REX-: U130.5 (Q2), U131.3 (I1)
/sun3_60_cpu/EMULATE-: U103.18 (IO2), U106.4 (I4)
/sun3_60_cpu/EN.BOOT-: IC1.6 (I/O_1), IC3.20 (I/O_10)
/sun3_60_cpu/EN.CTL-: IC1.9 (I/O_3), IC1.83 (I/O_47), IC3.45 (I/O_24)
/sun3_60_cpu/EN.FPP: IC3.92 (I/O_49), U103.6 (I6)
/sun3_60_cpu/PU.2a: R75.2, U15.7 (~PRE)
/sun3_60_cpu/PU.2b: R76.2, U17.7 (~PRE)
/sun3_60_cpu/PU.3a: R78.2, U15.6 (~CLR)
/sun3_60_cpu/PU.3b: R77.2, U17.6 (~CLR)
/sun3_60_cpu/R.CLK-: U106.9 (I9), U115.9 (~RCO)
/sun3_60_cpu/R.REQ-: U106.13 (IO7), U130.3 (D0)
/sun3_60_cpu/R.REX-: U130.2 (Q0), U131.2 (I0)
/sun3_60_cpu/S.REX-: U130.6 (Q4), U131.4 (I2)
/sun3_60_cpu/XACK5-: U130.12 (Q7), U130.14 (D5), U131.6 (I4)
/sun3_60_eeprom/CMCLK_32768_RTC: U302.10 (OIN), Y1.3 (OUT)
/sun3_60_eeprom/LED0: D1.1 (K), IC5.47 (I/O_26)
/sun3_60_eeprom/LED1: D2.1 (K), IC5.46 (I/O_25)
/sun3_60_eeprom/LED2: D3.1 (K), IC5.45 (I/O_24)
/sun3_60_eeprom/LED3: D4.1 (K), IC5.44 (I/O_23)
/sun3_60_eeprom/LED4: D5.1 (K), IC5.41 (I/0)
/sun3_60_eeprom/LED5: D6.1 (K), IC5.40 (I/O_22)
/sun3_60_eeprom/LED6: D7.1 (K), IC5.37 (I/O_21)
/sun3_60_eeprom/LED7: D8.1 (K), IC5.36 (I/O_20)
/sun3_60_eeprom/OE.EPROM-: IC4.44 (I/O_23), U300.22 (~OE)
/sun3_60_eeprom/RD.EEPROM-: IC4.97 (I/O_53), U301.25 (~OE)
/sun3_60_eeprom/RD.INT-: IC4.16 (I/O_7), IC5.20 (I/O_10)
/sun3_60_eeprom/RD.RTC-: IC4.19 (I/O_9), U302.24 (RD-)
/sun3_60_eeprom/RD.SCC0-: IC4.12 (I/O/PD1), U400.36 (~RD)
/sun3_60_eeprom/RD.SCC1-: IC4.10 (I/O_4), U401.36 (~RD)
/sun3_60_eeprom/WR.EEPROM-: IC4.98 (I/O_54), U301.31 (~WE)
/sun3_60_eeprom/WR.INT-: IC4.17 (I/O_8), IC5.19 (I/O_9)
/sun3_60_eeprom/WR.RTC-: IC4.20 (I/O_10), U302.1 (WR-)
/sun3_60_eeprom/WR.SCC0-: IC4.13 (I/O_5), U400.35 (~WR)
/sun3_60_eeprom/WR.SCC1-: IC4.9 (I/O_3), U401.35 (~WR)
/sun3_60_mmu_diag/ACCESS: IC1.64 (I/O_36), IC2.29 (I/O_14), U3.22 (I/O1)
/sun3_60_mmu_diag/CX3: IC3.81 (I/O_46), R3.2, U11.11
/sun3_60_mmu_diag/CX4: IC3.84 (I/O_48), U7.2 (A9), U8.15 (A5)
/sun3_60_mmu_diag/CX5: IC3.83 (I/O_47), U7.1 (A11), U8.16 (A4)
/sun3_60_mmu_diag/EN.PMAP0-: IC1.60 (I/O_33), IC2.32 (I/O_17)
/sun3_60_mmu_diag/EN.PMAP2-: IC1.58 (I/O_32), IC2.33 (I/O_18)
/sun3_60_mmu_diag/EN.PMAP3-: IC1.57 (I/O_31), IC2.35 (I/O_19)
/sun3_60_mmu_diag/EN.SMAP1-: IC1.61 (I/O_34), IC2.31 (I/O_16)
/sun3_60_mmu_diag/EN.SMAP-: IC1.63 (I/O_35), IC2.30 (I/O_15)
/sun3_60_mmu_diag/ENABLE_S3E_V: S2.C, U10.1 (S)
/sun3_60_mmu_diag/MMU0: IC2.6 (I/O_1), IC3.63 (I/O_35)
/sun3_60_mmu_diag/MMU1: IC2.8 (I/O_2), IC3.61 (I/O_34)
/sun3_60_mmu_diag/MMU2: IC2.9 (I/O_3), IC3.60 (I/O_33)
/sun3_60_mmu_diag/MMU3: IC2.10 (I/O_4), IC3.58 (I/O_32)
/sun3_60_mmu_diag/MMU4: IC2.12 (I/O/PD1), IC3.57 (I/O_31)
/sun3_60_mmu_diag/MMU5: IC2.13 (I/O_5), IC3.56 (I/O_30)
/sun3_60_mmu_diag/MMU6: IC2.14 (I/O_6), IC3.54 (I/O_29)
/sun3_60_mmu_diag/MMU7: IC2.16 (I/O_7), IC3.52 (I/O_28)
/sun3_60_mmu_diag/MMU.S: IC1.65 (I/O_37), IC2.17 (I/O_8), U4.23 (I/O2)
/sun3_60_mmu_diag/MMU.V: IC1.71 (I/O_41), IC2.20 (I/O_10), U4.21 (I/O0)
/sun3_60_mmu_diag/MMU.W: IC1.75 (I/O_42), IC2.19 (I/O_9), U4.22 (I/O1)
/sun3_60_mmu_diag/MMU.X: IC2.93 (I/O_50), U4.25 (I/O3)
/sun3_60_mmu_diag/MODIFY: IC1.67 (I/O_38), IC2.25 (I/O_13), U3.25 (I/O3)
/sun3_60_mmu_diag/RD.BERR-: IC1.79 (I/O_44), IC3.48 (I/O_27)
/sun3_60_mmu_diag/RD.CX-: IC1.85 (I/O/GCLK3), IC3.40 (I/O_22)
/sun3_60_mmu_diag/RD.ID-: IC1.8 (I/O_2), IC3.19 (I/O_9)
/sun3_60_mmu_diag/RD.SYSEN-: IC1.94 (I/O_51), IC3.35 (I/O_19)
/sun3_60_mmu_diag/S3E_A28: U7.7 (A15), U8.11 (A14), U10.12
/sun3_60_mmu_diag/S3E_A30: U7.6 (A18), U8.12 (A12), U10.9
/sun3_60_mmu_diag/S3E_CX3: U7.17 (A3), U8.20 (A0), U11.9
/sun3_60_mmu_diag/SA17: IC2.71 (I/O_41), U1.16 (A4), U2.16 (A4), U3.16 (A4), U4.16 (A4), U8.21 (I/O0)
/sun3_60_mmu_diag/SA18: IC2.69 (I/O_40), U1.15 (A5), U2.15 (A5), U3.15 (A5), U4.15 (A5), U8.22 (I/O1)
/sun3_60_mmu_diag/SA19: IC2.68 (I/O_39), U1.14 (A6), U2.14 (A6), U3.14 (A6), U4.14 (A6), U8.23 (I/O2)
/sun3_60_mmu_diag/SA20: IC2.67 (I/O_38), U1.13 (A7), U2.13 (A7), U3.13 (A7), U4.13 (A7), U8.25 (I/O3)
/sun3_60_mmu_diag/SA21: IC2.56 (I/O_30), U1.3 (A8), U2.3 (A8), U3.3 (A8), U4.3 (A8), U7.26 (I/O4)
/sun3_60_mmu_diag/SA22: IC2.57 (I/O_31), U1.2 (A9), U2.2 (A9), U3.2 (A9), U4.2 (A9), U7.27 (I/O5)
/sun3_60_mmu_diag/SA23: IC2.75 (I/O_42), U1.31 (A10), U2.31 (A10), U3.31 (A10), U4.31 (A10), U7.29 (I/O7)
/sun3_60_mmu_diag/SA24: IC2.58 (I/O_32), U1.1 (A11), U2.1 (A11), U3.1 (A11), U4.1 (A11), U7.28 (I/O6)
/sun3_60_mmu_diag/SA25: IC2.65 (I/O_37), R55.1, U1.12 (A12), U2.12 (A12), U3.12 (A12), U4.12 (A12), U8.26 (I/O4)
/sun3_60_mmu_diag/SA26: IC2.64 (I/O_36), R56.1, U1.11 (A14), U2.11 (A14), U3.11 (A14), U4.11 (A14), U8.27 (I/O5)
/sun3_60_mmu_diag/SA27: IC2.54 (I/O_29), R57.1, U1.4 (A13), U2.4 (A13), U3.4 (A13), U4.4 (A13), U7.25 (I/O3)
/sun3_60_mmu_diag/SA28: IC2.60 (I/O_33), R58.1, U1.7 (A15), U2.7 (A15), U3.7 (A15), U4.7 (A15), U7.22 (I/O1)
/sun3_60_mmu_diag/SA29: IC2.63 (I/O_35), R59.1, U1.10 (A16), U2.10 (A16), U3.10 (A16), U4.10 (A16), U8.28 (I/O6)
/sun3_60_mmu_diag/SA30: IC2.61 (I/O_34), R60.1, U1.9 (A17), U2.9 (A17), U3.9 (A17), U4.9 (A17), U7.21 (I/O0)
/sun3_60_mmu_diag/SA31: IC2.52 (I/O_28), R61.1, U1.6 (A18), U2.6 (A18), U3.6 (A18), U4.6 (A18), U7.23 (I/O2)
/sun3_60_mmu_diag/TYPE0: IC1.69 (I/O_40), IC2.21 (I/O_11), IC4.85 (I/O/GCLK3), U3.21 (I/O0)
/sun3_60_mmu_diag/TYPE1: IC1.68 (I/O_39), IC2.23 (I/O_12), IC4.84 (I/O_48), U3.23 (I/O2)
/sun3_60_mmu_diag/WE.PMAP0-: IC1.96 (I/O_52), IC1.97 (I/O_53), U4.5 (~WE)
/sun3_60_mmu_diag/WE.PMAP2-: IC1.54 (I/O_29), U2.5 (~WE)
/sun3_60_mmu_diag/WE.PMAP3-: IC1.56 (I/O_30), U1.5 (~WE)
/sun3_60_mmu_diag/WE.SMAP1-: IC1.99 (I/O_55), U8.5 (~WE)
/sun3_60_mmu_diag/WE.SMAP-: IC1.98 (I/O_54), U7.5 (~WE)
/sun3_60_mmu_diag/WE.STAT-: IC1.76 (I/O_43), U3.5 (~WE)
/sun3_60_mmu_diag/WR.CX-: IC1.84 (I/O_48), IC3.44 (I/O_23)
/sun3_60_mmu_diag/WR.SYSEN-: IC1.93 (I/O_50), IC3.36 (I/O_20)
/sun3_60_serial/RXDC: J6.3, U401.13 (RXDA)
/sun3_60_serial/RXDD: J7.3, U401.27 (RXDB)
/sun3_60_serial/RxDA: J3.6, U404.3
/sun3_60_serial/RxDB: J3.4, U404.9
/sun3_60_serial/SERIAL_PCLK: U400.20 (PCLK), U401.20 (PCLK), U402.8 (OUT)
/sun3_60_serial/TXDC: J6.2, U401.15 (TXDA)
/sun3_60_serial/TXDD: J7.2, U401.25 (TXDB)
/sun3_60_serial/TxDA: J3.5, U404.2
/sun3_60_serial/TxDB: J3.7, U404.6
ENABLE_S3E: IC1.100 (I/O_56), IC3.87 (INPUT/GCLK1), S1.C, U11.1 (S)
GND: C1.2, C2.2, C3.2, C4.2, C5.2, C6.2, C7.2, C8.2, C9.2, C10.2, C11.2, C12.2, C13.2, C14.2, C15.2, C16.2, C17.2, C18.2, C19.2, C20.2, C21.2, C22.2, C23.2, C24.2, C25.2, C26.2, C27.2, C28.2, C29.2, C30.2, C31.2, C32.2, C33.2, C34.2, C35.2, C36.2, C37.2, C38.2, C39.2, C40.2, C41.2, C42.2, C43.2, C44.2, C45.2, C46.2, C47.2, C48.2, C49.2, C50.2, C51.2, C52.2, C61.2, C62.2, C63.2, C64.2, C65.2, C66.2, C67.2, C68.2, C199.2, C502.1, C503.2, C504.2, C505.2, IC1.11 (GND_1), IC1.26 (GND_2), IC1.38 (GND_3), IC1.43 (GND_4), IC1.59 (GND_5), IC1.74 (GND_6), IC1.86 (GND_7), IC1.95 (GND_8), IC2.11 (GND_1), IC2.26 (GND_2), IC2.38 (GND_3), IC2.43 (GND_4), IC2.59 (GND_5), IC2.74 (GND_6), IC2.86 (GND_7), IC2.95 (GND_8), IC3.11 (GND_1), IC3.26 (GND_2), IC3.38 (GND_3), IC3.43 (GND_4), IC3.59 (GND_5), IC3.74 (GND_6), IC3.86 (GND_7), IC3.95 (GND_8), IC4.11 (GND_1), IC4.26 (GND_2), IC4.38 (GND_3), IC4.43 (GND_4), IC4.59 (GND_5), IC4.74 (GND_6), IC4.86 (GND_7), IC4.95 (GND_8), IC5.11 (GND_1), IC5.26 (GND_2), IC5.38 (GND_3), IC5.43 (GND_4), IC5.59 (GND_5), IC5.74 (GND_6), IC5.86 (GND_7), IC5.95 (GND_8), IC6.11 (GND_1), IC6.26 (GND_2), IC6.38 (GND_3), IC6.43 (GND_4), IC6.59 (GND_5), IC6.74 (GND_6), IC6.86 (GND_7), IC6.95 (GND_8), IC8.11 (GND_1), IC8.26 (GND_2), IC8.38 (GND_3), IC8.43 (GND_4), IC8.59 (GND_5), IC8.74 (GND_6), IC8.86 (GND_7), IC8.95 (GND_8), J3.1, J3.2, J5.1, J5.MH1, J5.MH2, J6.7, J7.7, J11.2, J11.3, K199.2, K500.2, K900.2, K901.2, K903.2, K904.2, R2.1, R3.1, R5.1, R55.2, R56.2, R57.2, R58.2, R59.2, R60.2, R61.2, R70.1, R71.1, R72.1, R101.2, U1.24 (GND), U1.32 (~OE), U2.24 (GND), U2.32 (~OE), U3.24 (GND), U3.32 (~OE), U4.24 (GND), U4.32 (~OE), U7.24 (GND), U7.32 (~OE), U8.24 (GND), U8.32 (~OE), U10.2, U10.3, U10.5, U10.6, U10.8 (GND), U10.10, U10.13, U10.15 (~OE), U11.2, U11.3, U11.5, U11.6, U11.8 (GND), U11.10, U11.13, U11.14, U11.15 (~OE), U14.3 (GND), U15.4 (GND), U16.2 (GND), U17.4 (GND), U100.A10 (GND), U100.B1 (GND), U100.B9 (GND), U100.C3 (GND), U100.F12 (GND), U100.G12 (GND), U100.H2 (AVEC-), U100.H13 (GND), U100.J3 (GND), U100.K1 (GND), U100.K3 (GND), U100.L7 (GND), U100.L11 (GND), U100.N7 (GND), U101.A2 (GND), U101.A10 (GND), U101.B2 (GND), U101.B3 (GND), U101.B4 (~SENSE), U101.B7 (GND), U101.C1 (GND), U101.C3 (GND), U101.D2 (GND), U101.E10 (GND), U101.F2 (GND), U101.H9 (GND), U101.J8 (GND), U101.K3 (GND), U103.10 (GND), U104.7 (GND), U106.10 (GND), U108.7 (GND), U110.7 (GND), U115.8 (GND), U115.12 (~CE), U115.14 (~OE), U130.10 (GND), U131.10 (GND), U132.10 (GND), U199.4 (GND), U300.14 (GND), U300.20 (~CE), U301.3 (A12), U301.16 (GND), U301.23 (~CS), U301.27 (A11), U302.3 (CS-), U302.11 (INTSRC), U302.13 (GND), U400.12 (~RTXCA)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
unnamed: C502.2, R502.2
unnamed: D1.2 (A), R62.1
unnamed: D2.2 (A), R63.1
unnamed: D3.2 (A), R64.1
unnamed: D4.2 (A), R65.1
unnamed: D5.2 (A), R66.1
unnamed: D6.2 (A), R67.1
unnamed: D7.2 (A), R68.1
unnamed: D8.2 (A), R69.1
unnamed: R1.2, S1.1
unnamed: R2.2, S1.2
unnamed: R4.2, S2.1
unnamed: R5.2, S2.2
unnamed: U108.3, U108.4
unnamed: U108.1, U110.8 (OUT)
unnamed: K199.1, U199.3 (CT)
unnamed: C199.1, U199.1 (REF)
unnamed: R301.1, U302.14 (VBAK), X301.2
unnamed: R301.2, U309.2 (-)
unnamed: U400.13 (RXDA), U404.4
unnamed: U400.27 (RXDB), U404.8
unnamed: U400.15 (TXDA), U404.1
unnamed: U400.25 (TXDB), U404.5
unnamed: C505.1, U501.17 (PF)
unnamed: C504.1, U501.16 (RF)
unnamed: R501.1, R502.1, U501.5 (TSEL)
unnamed: U108.11, U803.9 (D1)
VCC: C1.1, C2.1, C3.1, C4.1, C5.1, C6.1, C7.1, C8.1, C9.1, C10.1, C11.1, C12.1, C13.1, C14.1, C15.1, C16.1, C17.1, C18.1, C19.1, C20.1, C21.1, C22.1, C23.1, C24.1, C25.1, C26.1, C27.1, C28.1, C29.1, C30.1, C31.1, C32.1, C33.1, C34.1, C35.1, C36.1, C37.1, C38.1, C39.1, C40.1, C41.1, C42.1, C43.1, C44.1, C45.1, C46.1, C47.1, C48.1, C49.1, C50.1, C51.1, C52.1, C61.1, C62.1, C63.1, C64.1, C65.1, C66.1, C67.1, C68.1, C503.1, IC1.3 (VCCIO_1), IC1.18 (VCCIO_2), IC1.34 (VCCIO_3), IC1.39 (VCCINT_1), IC1.51 (VCCIO_4), IC1.66 (VCCIO_5), IC1.82 (VCCIO_6), IC1.91 (VCCINT_2), IC2.3 (VCCIO_1), IC2.18 (VCCIO_2), IC2.34 (VCCIO_3), IC2.39 (VCCINT_1), IC2.51 (VCCIO_4), IC2.66 (VCCIO_5), IC2.82 (VCCIO_6), IC2.91 (VCCINT_2), IC3.3 (VCCIO_1), IC3.18 (VCCIO_2), IC3.34 (VCCIO_3), IC3.39 (VCCINT_1), IC3.51 (VCCIO_4), IC3.66 (VCCIO_5), IC3.82 (VCCIO_6), IC3.91 (VCCINT_2), IC4.3 (VCCIO_1), IC4.18 (VCCIO_2), IC4.34 (VCCIO_3), IC4.39 (VCCINT_1), IC4.51 (VCCIO_4), IC4.66 (VCCIO_5), IC4.82 (VCCIO_6), IC4.91 (VCCINT_2), IC5.3 (VCCIO_1), IC5.18 (VCCIO_2), IC5.34 (VCCIO_3), IC5.39 (VCCINT_1), IC5.51 (VCCIO_4), IC5.66 (VCCIO_5), IC5.82 (VCCIO_6), IC5.91 (VCCINT_2), IC6.3 (VCCIO_1), IC6.18 (VCCIO_2), IC6.34 (VCCIO_3), IC6.39 (VCCINT_1), IC6.51 (VCCIO_4), IC6.66 (VCCIO_5), IC6.82 (VCCIO_6), IC6.91 (VCCINT_2), IC8.3 (VCCIO_1), IC8.18 (VCCIO_2), IC8.34 (VCCIO_3), IC8.39 (VCCINT_1), IC8.51 (VCCIO_4), IC8.66 (VCCIO_5), IC8.82 (VCCIO_6), IC8.91 (VCCINT_2), J3.3, J3.8, J11.4, K500.1, K900.1, K901.1, K903.1, K904.1, R1.1, R4.1, R22.1, R23.1, R24.1, R25.1, R26.1, R27.1, R28.1, R29.1, R30.1, R31.1, R32.1, R33.1, R34.1, R35.1, R36.1, R37.1, R38.1, R39.1, R40.1, R41.1, R42.1, R43.1, R44.1, R45.1, R46.1, R47.1, R48.1, R49.1, R50.1, R51.1, R52.1, R53.1, R62.2, R63.2, R64.2, R65.2, R66.2, R67.2, R68.2, R69.2, R75.1, R76.1, R77.1, R78.1, R100.1, R501.2, U1.8 (VDD), U2.8 (VDD), U3.8 (VDD), U4.8 (VDD), U7.8 (VDD), U8.8 (VDD), U10.16 (VCC), U11.16 (VCC), U14.5 (VCC), U15.8 (VCC), U16.4 (VCC), U17.8 (VCC), U100.A9 (VCC), U100.D1 (VCC), U100.D2 (VCC), U100.D3 (VCC), U100.E3 (VCC), U100.G11 (VCC), U100.G13 (VCC), U100.M8 (VCC), U100.N8 (VCC), U100.N13 (VCC), U101.A1 (VCC), U101.B1 (VCC), U101.B8 (VCC), U101.E2 (VCC), U101.E9 (VCC), U101.F1 (Size-), U101.H3 (A00), U101.H8 (VCC), U101.J2 (VCC), U103.20 (VCC), U104.14 (VCC), U106.20 (VCC), U108.10, U108.14 (VCC), U110.14 (Vcc), U115.10 (~MRC), U115.16 (VCC), U130.20 (VCC), U131.20 (VCC), U132.2 (1A1), U132.4 (1A2), U132.6 (1A3), U132.8 (1A4), U132.11 (2A1), U132.13 (2A2), U132.15 (2A3), U132.17 (2A4), U132.20 (VCC), U199.2 (RI-), U199.7 (SI), U199.8 (VCC), U300.28 (VCC), U301.32 (VCC), U302.2 (ALE), U302.23 (VCC), U309.1 (+), U400.7 (IEI), U400.8 (~INTACK)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

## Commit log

2025-06-09 fix wrong polarity on TEST1, comments
2025-06-13 typo
2025-06-14 fix comments on A0/A1 use for PMAP update; it's all about long access & bus sizing
2025-06-14 PMAP1, missing GND
2025-06-14 First draft for an expanded MMU
    This version uses vintage parts except for the SRAM, which are IS61C5128AS-25HLI (they could be QLI instead)
    Unfortunately, this requires:
    * 2 more 74ALS245 to buffer the second byte of PMAP indices in the SMAP
    * one more LS2518 (!) to extend the context register
    * a couple of 74CBTLV3257 to be able to stay in "normal" Sun3 mode with minimal delays on the signals
    * a couple of switches to enabled/disable the new features
2025-06-15 remove letofver ALS245 (data for the 2nd byte of index will come from the upper byte like evrything else) ; update comment for U231, U102 also need modifications
2025-06-15 commit a bunch of in-progress PLD for documentation
2025-06-15 more comments
2025-07-06 cleanup (?)
2025-07-27 draft, ugly and WiP
2025-08-07 ongoing ethernet pld
2025-08-08 ongoing
2025-09-13 update (lost cause?)
